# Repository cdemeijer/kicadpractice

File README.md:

Going through the [books provided by ai03](https://wiki.ai03.com/books/pcb-design). Using KiCad 7.0.9 instead of the recommended older version.

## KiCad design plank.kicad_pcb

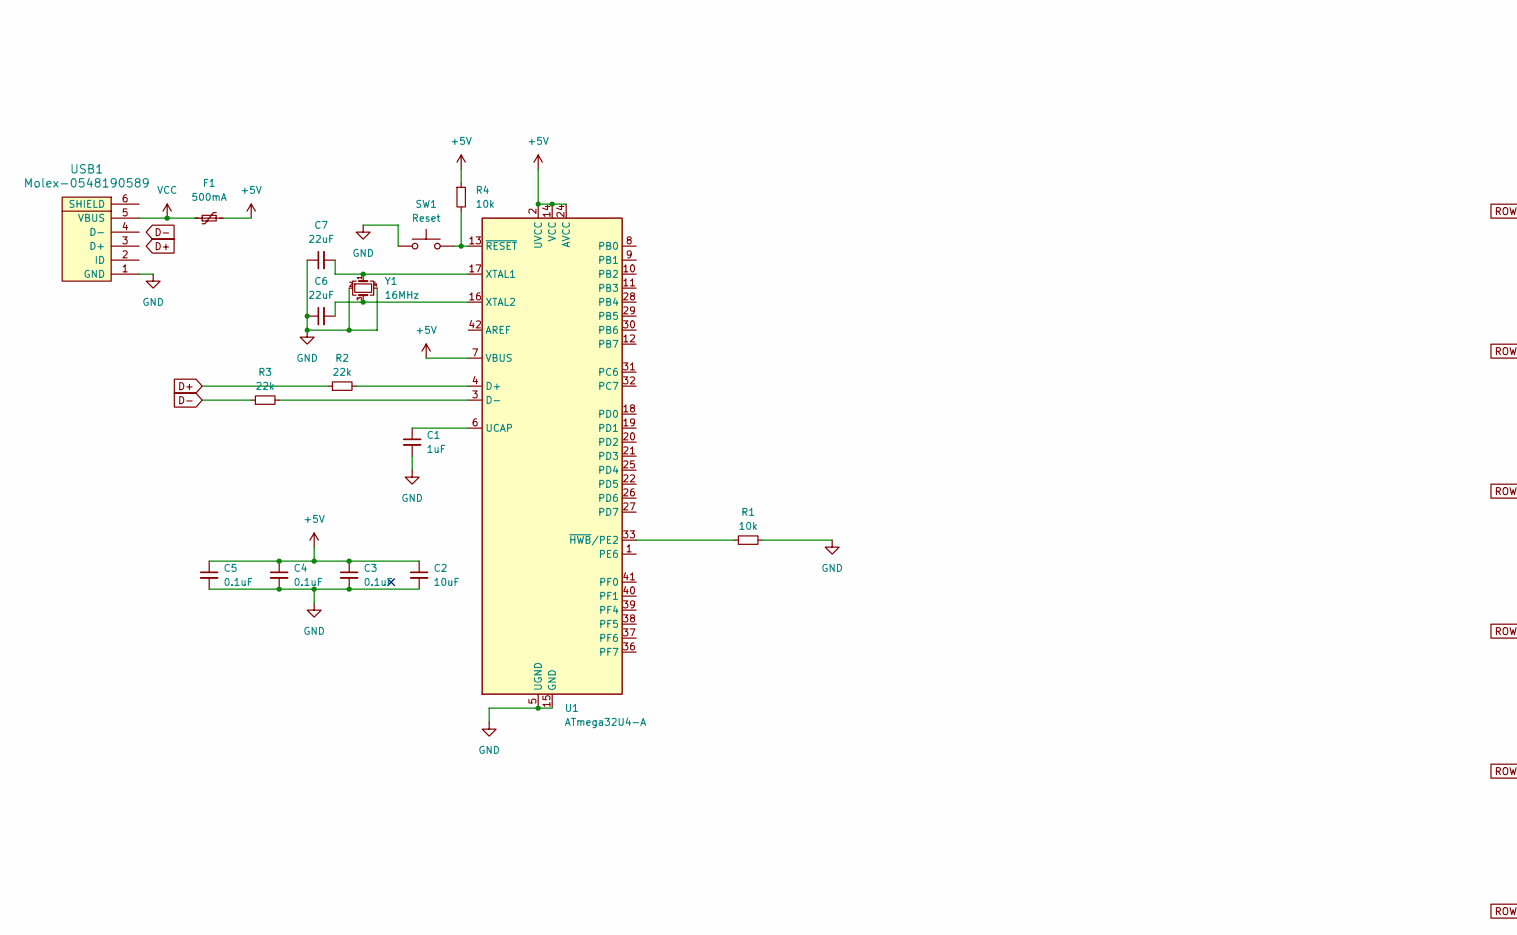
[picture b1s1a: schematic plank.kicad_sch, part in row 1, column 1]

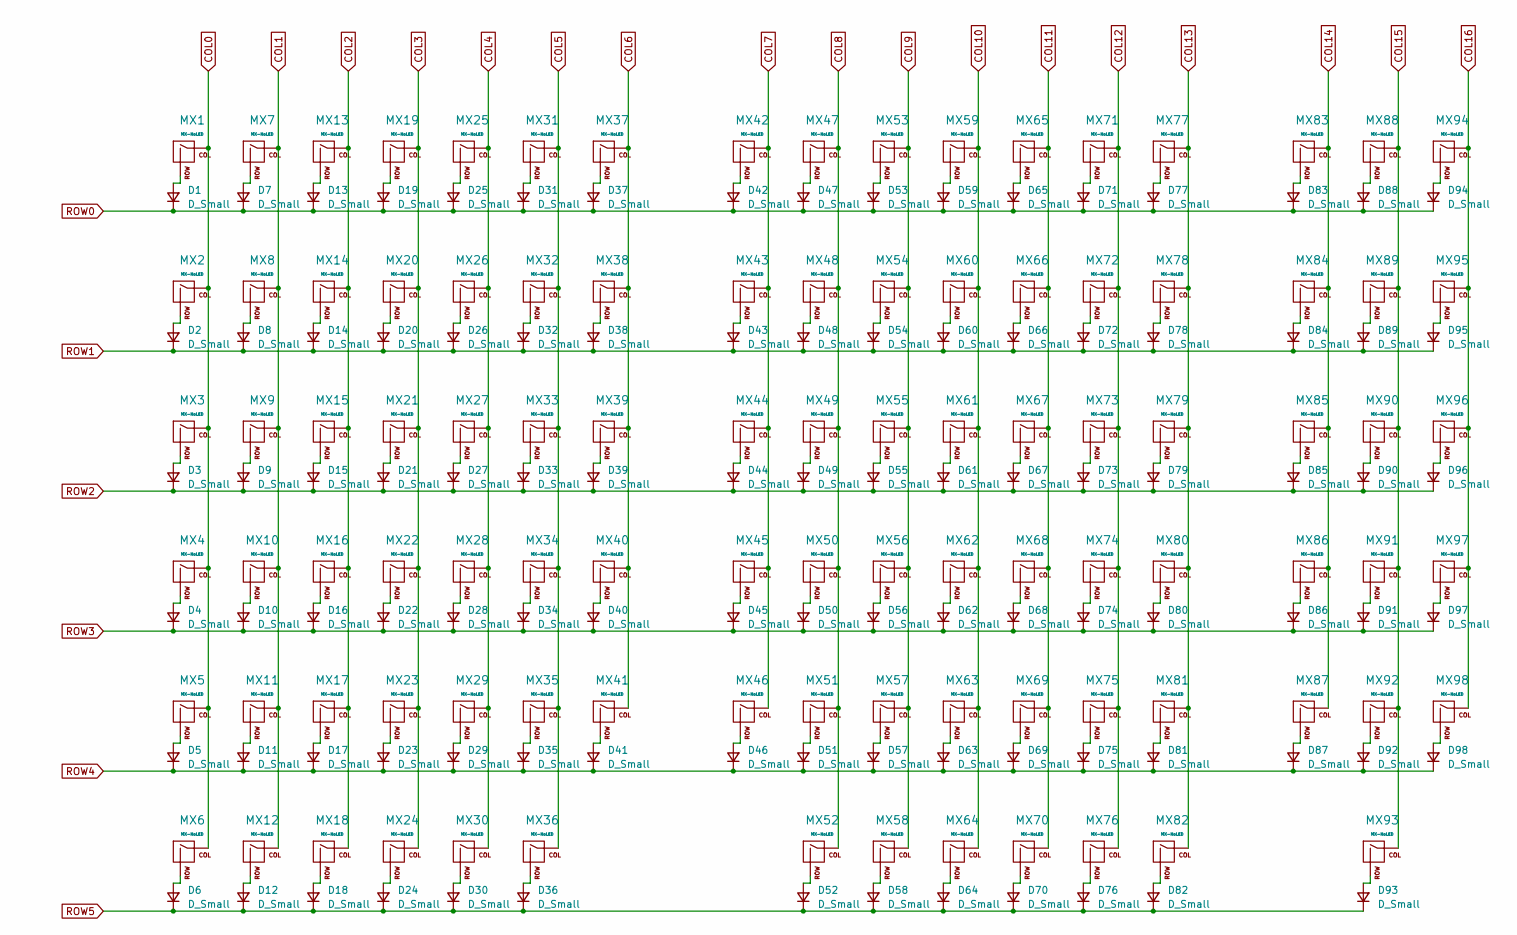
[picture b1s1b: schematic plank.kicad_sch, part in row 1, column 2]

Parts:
C1: 1uF; C_0805_2012Metric
C2: 10uF; C_0805_2012Metric
C3, C4, C5: 0.1uF; C_0805_2012Metric
C6, C7: 22uF; C_0805_2012Metric
D1, D2, D3, D4, D5, D6, D7, D8, D9, D10, D11, D12, D13, D14, D15, D16, D17, D18, D19, D20, D21, D22, D23, D24, D25, D26, D27, D28, D29, D30, D31, D32, D33, D34, D35, D36, D37, D38, D39, D40, D41, D42, D43, D44, D45, D46, D47, D48, D49, D50, D51, D52, D53, D54, D55, D56, D57, D58, D59, D60, D61, D62, D63, D64, D65, D66, D67, D68, D69, D70, D71, D72, D73, D74, D75, D76, D77, D78, D79, D80, D81, D82, D83, D84, D85, D86, D87, D88, D89, D90, D91, D92, D93, D94, D95, D96, D97, D98: D_Small; D_SOD-123
F1: 500mA; Fuse_1206_3216Metric
MX1, MX2, MX3, MX4, MX5, MX6, MX7, MX8, MX9, MX10, MX11, MX12, MX13, MX14, MX15, MX16, MX17, MX18, MX19, MX20, MX21, MX22, MX23, MX24, MX25, MX26, MX27, MX28, MX29, MX30, MX31, MX32, MX33, MX34, MX35, MX36, MX37, MX38, MX39, MX40, MX41, MX42, MX43, MX44, MX45, MX46, MX47, MX48, MX49, MX50, MX51, MX52, MX53, MX54, MX55, MX56, MX57, MX58, MX59, MX60, MX61, MX62, MX63, MX64, MX65, MX66, MX67, MX68, MX69, MX70, MX71, MX72, MX73, MX74, MX75, MX76, MX77, MX78, MX79, MX80, MX81, MX82, MX83, MX84, MX85, MX86, MX87, MX88, MX89, MX90, MX91, MX92, MX93, MX94, MX95, MX96, MX97, MX98: MX-NoLED; SW_Cherry_MX_1.00u_PCB
R1, R4: 10k; R_0805_2012Metric
R2, R3: 22k; R_0805_2012Metric
SW1: Reset; Panasonic_EVQPUJ_EVQPUA
U1: ATmega32U4-A; TQFP-44_10x10mm_P0.8mm
USB1: Molex-0548190589; Molex_SL_171971-0006_1x06_P2.54mm_Vertical
Y1: 16MHz; Crystal_SMD_3225-4Pin_3.2x2.5mm

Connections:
+5V: C2.1, C3.1, C4.1, C5.1, F1.2, R4.1, U1.2 (UVCC), U1.7 (VBUS), U1.14 (VCC), U1.24 (AVCC), U1.34 (VCC), U1.44 (AVCC)
COL0: MX1.1 (COL), MX2.1 (COL), MX3.1 (COL), MX4.1 (COL), MX5.1 (COL), MX6.1 (COL)
COL1: MX7.1 (COL), MX8.1 (COL), MX9.1 (COL), MX10.1 (COL), MX11.1 (COL), MX12.1 (COL)
COL2: MX13.1 (COL), MX14.1 (COL), MX15.1 (COL), MX16.1 (COL), MX17.1 (COL), MX18.1 (COL)
COL3: MX19.1 (COL), MX20.1 (COL), MX21.1 (COL), MX22.1 (COL), MX23.1 (COL), MX24.1 (COL)
COL4: MX25.1 (COL), MX26.1 (COL), MX27.1 (COL), MX28.1 (COL), MX29.1 (COL), MX30.1 (COL)
COL5: MX31.1 (COL), MX32.1 (COL), MX33.1 (COL), MX34.1 (COL), MX35.1 (COL), MX36.1 (COL)
COL6: MX37.1 (COL), MX38.1 (COL), MX39.1 (COL), MX40.1 (COL), MX41.1 (COL)
COL7: MX42.1 (COL), MX43.1 (COL), MX44.1 (COL), MX45.1 (COL), MX46.1 (COL)
COL8: MX47.1 (COL), MX48.1 (COL), MX49.1 (COL), MX50.1 (COL), MX51.1 (COL), MX52.1 (COL)
COL9: MX53.1 (COL), MX54.1 (COL), MX55.1 (COL), MX56.1 (COL), MX57.1 (COL), MX58.1 (COL)
COL10: MX59.1 (COL), MX60.1 (COL), MX61.1 (COL), MX62.1 (COL), MX63.1 (COL), MX64.1 (COL)
COL11: MX65.1 (COL), MX66.1 (COL), MX67.1 (COL), MX68.1 (COL), MX69.1 (COL), MX70.1 (COL)
COL12: MX71.1 (COL), MX72.1 (COL), MX73.1 (COL), MX74.1 (COL), MX75.1 (COL), MX76.1 (COL)
COL13: MX77.1 (COL), MX78.1 (COL), MX79.1 (COL), MX80.1 (COL), MX81.1 (COL), MX82.1 (COL)
COL14: MX83.1 (COL), MX84.1 (COL), MX85.1 (COL), MX86.1 (COL), MX87.1 (COL)
COL15: MX88.1 (COL), MX89.1 (COL), MX90.1 (COL), MX91.1 (COL), MX92.1 (COL), MX93.1 (COL)
COL16: MX94.1 (COL), MX95.1 (COL), MX96.1 (COL), MX97.1 (COL), MX98.1 (COL)
D+: R2.1
D-: R3.1
GND: C1.2, C2.2, C3.2, C4.2, C5.2, C6.1, C7.1, R1.2, SW1.1, U1.5 (UGND), U1.15 (GND), U1.23 (GND), U1.35 (GND), U1.43 (GND), USB1.1 (GND), Y1.2, Y1.4
unnamed: D1.2 (A), MX1.2 (ROW)
unnamed: D2.2 (A), MX2.2 (ROW)
unnamed: D3.2 (A), MX3.2 (ROW)
unnamed: D4.2 (A), MX4.2 (ROW)
unnamed: D5.2 (A), MX5.2 (ROW)
unnamed: D6.2 (A), MX6.2 (ROW)
unnamed: D7.2 (A), MX7.2 (ROW)
unnamed: D8.2 (A), MX8.2 (ROW)
unnamed: D9.2 (A), MX9.2 (ROW)
unnamed: D10.2 (A), MX10.2 (ROW)
unnamed: D11.2 (A), MX11.2 (ROW)
unnamed: D12.2 (A), MX12.2 (ROW)
unnamed: D13.2 (A), MX13.2 (ROW)
unnamed: D14.2 (A), MX14.2 (ROW)
unnamed: D15.2 (A), MX15.2 (ROW)
unnamed: D16.2 (A), MX16.2 (ROW)
unnamed: D17.2 (A), MX17.2 (ROW)
unnamed: D18.2 (A), MX18.2 (ROW)
unnamed: D19.2 (A), MX19.2 (ROW)
unnamed: D20.2 (A), MX20.2 (ROW)
unnamed: D21.2 (A), MX21.2 (ROW)
unnamed: D22.2 (A), MX22.2 (ROW)
unnamed: D23.2 (A), MX23.2 (ROW)
unnamed: D24.2 (A), MX24.2 (ROW)
unnamed: D25.2 (A), MX25.2 (ROW)
unnamed: D26.2 (A), MX26.2 (ROW)
unnamed: D27.2 (A), MX27.2 (ROW)
unnamed: D28.2 (A), MX28.2 (ROW)
unnamed: D29.2 (A), MX29.2 (ROW)
unnamed: D30.2 (A), MX30.2 (ROW)
unnamed: D31.2 (A), MX31.2 (ROW)
unnamed: D32.2 (A), MX32.2 (ROW)
unnamed: D33.2 (A), MX33.2 (ROW)
unnamed: D34.2 (A), MX34.2 (ROW)
unnamed: D35.2 (A), MX35.2 (ROW)
unnamed: D36.2 (A), MX36.2 (ROW)
unnamed: D37.2 (A), MX37.2 (ROW)
unnamed: D38.2 (A), MX38.2 (ROW)
unnamed: D39.2 (A), MX39.2 (ROW)
unnamed: D40.2 (A), MX40.2 (ROW)
unnamed: D41.2 (A), MX41.2 (ROW)
unnamed: D42.2 (A), MX42.2 (ROW)
unnamed: D43.2 (A), MX43.2 (ROW)
unnamed: D44.2 (A), MX44.2 (ROW)
unnamed: D45.2 (A), MX45.2 (ROW)
unnamed: D46.2 (A), MX46.2 (ROW)
unnamed: D47.2 (A), MX47.2 (ROW)
unnamed: D48.2 (A), MX48.2 (ROW)
unnamed: D49.2 (A), MX49.2 (ROW)
unnamed: D50.2 (A), MX50.2 (ROW)
unnamed: D51.2 (A), MX51.2 (ROW)
unnamed: D52.2 (A), MX52.2 (ROW)
unnamed: D53.2 (A), MX53.2 (ROW)
unnamed: D54.2 (A), MX54.2 (ROW)
unnamed: D55.2 (A), MX55.2 (ROW)
unnamed: D56.2 (A), MX56.2 (ROW)
unnamed: D57.2 (A), MX57.2 (ROW)
unnamed: D58.2 (A), MX58.2 (ROW)
unnamed: D59.2 (A), MX59.2 (ROW)
unnamed: D60.2 (A), MX60.2 (ROW)
unnamed: D61.2 (A), MX61.2 (ROW)
unnamed: D62.2 (A), MX62.2 (ROW)
unnamed: D63.2 (A), MX63.2 (ROW)
unnamed: D64.2 (A), MX64.2 (ROW)
unnamed: D65.2 (A), MX65.2 (ROW)
unnamed: D66.2 (A), MX66.2 (ROW)
unnamed: D67.2 (A), MX67.2 (ROW)
unnamed: D68.2 (A), MX68.2 (ROW)
unnamed: D69.2 (A), MX69.2 (ROW)
unnamed: D70.2 (A), MX70.2 (ROW)
unnamed: D71.2 (A), MX71.2 (ROW)
unnamed: D72.2 (A), MX72.2 (ROW)
unnamed: D73.2 (A), MX73.2 (ROW)
unnamed: D74.2 (A), MX74.2 (ROW)
unnamed: D75.2 (A), MX75.2 (ROW)
unnamed: D76.2 (A), MX76.2 (ROW)
unnamed: D77.2 (A), MX77.2 (ROW)
unnamed: D78.2 (A), MX78.2 (ROW)
unnamed: D79.2 (A), MX79.2 (ROW)
unnamed: D80.2 (A), MX80.2 (ROW)
unnamed: D81.2 (A), MX81.2 (ROW)
unnamed: D82.2 (A), MX82.2 (ROW)
unnamed: D83.2 (A), MX83.2 (ROW)
unnamed: D84.2 (A), MX84.2 (ROW)
unnamed: D85.2 (A), MX85.2 (ROW)
unnamed: D86.2 (A), MX86.2 (ROW)
unnamed: D87.2 (A), MX87.2 (ROW)
unnamed: D88.2 (A), MX88.2 (ROW)
unnamed: D89.2 (A), MX89.2 (ROW)
unnamed: D90.2 (A), MX90.2 (ROW)
unnamed: D91.2 (A), MX91.2 (ROW)
unnamed: D92.2 (A), MX92.2 (ROW)
unnamed: D93.2 (A), MX93.2 (ROW)
unnamed: D94.2 (A), MX94.2 (ROW)
unnamed: D95.2 (A), MX95.2 (ROW)
unnamed: D96.2 (A), MX96.2 (ROW)
unnamed: D97.2 (A), MX97.2 (ROW)
unnamed: D98.2 (A), MX98.2 (ROW)
unnamed: R2.2, U1.4 (D+)
unnamed: R3.2, U1.3 (D-)
unnamed: C1.1, U1.6 (UCAP)
unnamed: C7.2, U1.17 (XTAL1), Y1.1
unnamed: C6.2, U1.16 (XTAL2), Y1.3
unnamed: R1.1, U1.33 (~HWB/PE2)
unnamed: R4.2, SW1.2, U1.13 (~RESET)
ROW0: D1.1 (K), D7.1 (K), D13.1 (K), D19.1 (K), D25.1 (K), D31.1 (K), D37.1 (K), D42.1 (K), D47.1 (K), D53.1 (K), D59.1 (K), D65.1 (K), D71.1 (K), D77.1 (K), D83.1 (K), D88.1 (K), D94.1 (K)
ROW1: D2.1 (K), D8.1 (K), D14.1 (K), D20.1 (K), D26.1 (K), D32.1 (K), D38.1 (K), D43.1 (K), D48.1 (K), D54.1 (K), D60.1 (K), D66.1 (K), D72.1 (K), D78.1 (K), D84.1 (K), D89.1 (K), D95.1 (K)
ROW2: D3.1 (K), D9.1 (K), D15.1 (K), D21.1 (K), D27.1 (K), D33.1 (K), D39.1 (K), D44.1 (K), D49.1 (K), D55.1 (K), D61.1 (K), D67.1 (K), D73.1 (K), D79.1 (K), D85.1 (K), D90.1 (K), D96.1 (K)
ROW3: D4.1 (K), D10.1 (K), D16.1 (K), D22.1 (K), D28.1 (K), D34.1 (K), D40.1 (K), D45.1 (K), D50.1 (K), D56.1 (K), D62.1 (K), D68.1 (K), D74.1 (K), D80.1 (K), D86.1 (K), D91.1 (K), D97.1 (K)
ROW4: D5.1 (K), D11.1 (K), D17.1 (K), D23.1 (K), D29.1 (K), D35.1 (K), D41.1 (K), D46.1 (K), D51.1 (K), D57.1 (K), D63.1 (K), D69.1 (K), D75.1 (K), D81.1 (K), D87.1 (K), D92.1 (K), D98.1 (K)
ROW5: D6.1 (K), D12.1 (K), D18.1 (K), D24.1 (K), D30.1 (K), D36.1 (K), D52.1 (K), D58.1 (K), D64.1 (K), D70.1 (K), D76.1 (K), D82.1 (K), D93.1 (K)
VCC: F1.1, USB1.5 (VBUS)

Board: 2 copper layers, 212 parts (0 on the bottom side), 131 nets, no tracks yet.

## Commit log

2023-12-02 Start README.md
2023-12-02 Initial generated files
2023-12-02 Added library submodules
2023-12-02 Added footprints and symbols libraries
2023-12-03 Wired Atmega32U4-A
2023-12-03 Added USB Molex
2023-12-03 Added switch matrix
2023-12-03 Started the PCB layout
2023-12-06 Switches in place
2023-12-06 Added edge and bolt locations
